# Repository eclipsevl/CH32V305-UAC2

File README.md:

# CH32V305-UAC2
ch32v305fbp6 + es9018k2m + opa1678 usb dac  

Due to using inexpensive components, the clock has approximately a 200 Hz error. Additionally, the MCLK GPIO speed exceeds the maximum 50 MHz limit at 192 kHz.  
If desired, you can use an external crystal for the I2S MCLK clock.  
This dac only support 48k,96k,192k 32bits, dsd and other formats are not considered.  
This DAC only supports high-speed connections.  
You might hear some popping sounds during sudden high-load tasks. I have added mute detection code to eliminate some of these occurrences. I hope it helps you. You can adjust your parameters in config.h.  

> [!NOTE]
> ch32v305fbp6 doesn't have OTG-HS(but it has OTG-FS), so you can't connect this project to a smartphone.  

## setup
Just flash HSDAC.elf to hardware. Don't use HID-Bootloader and dfu, they will be redoing in future.  

## help wanted
Can someone redesign the power amplifier circuit?  

# IMAGE

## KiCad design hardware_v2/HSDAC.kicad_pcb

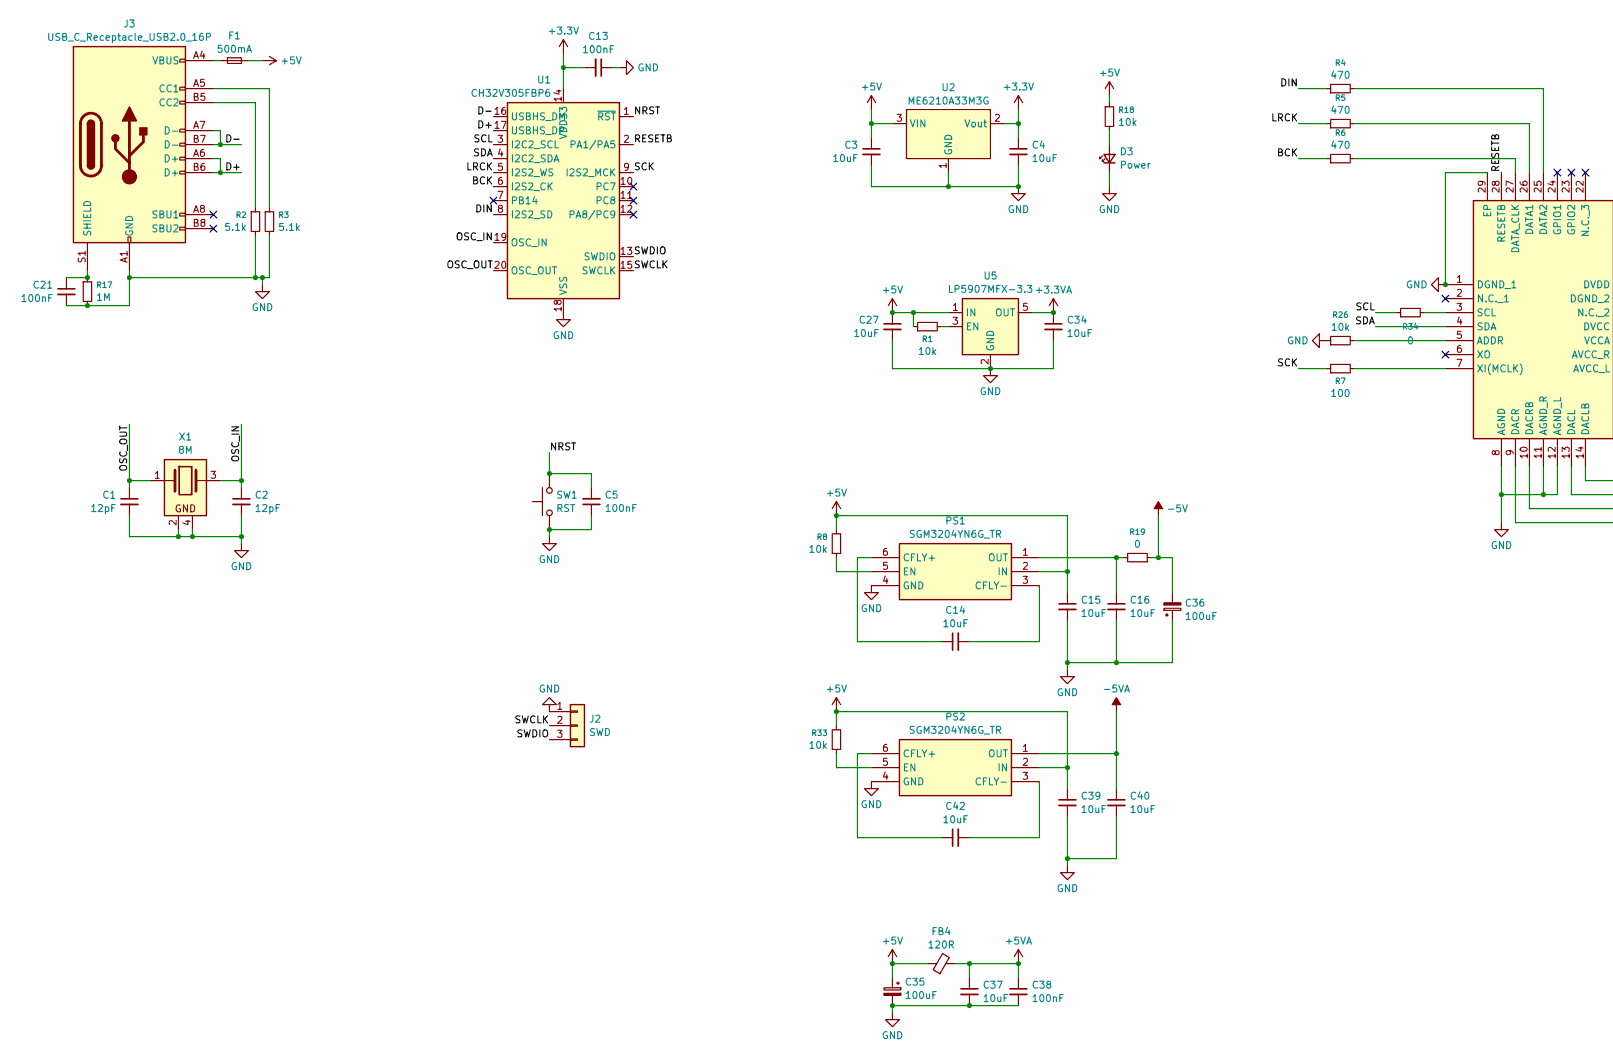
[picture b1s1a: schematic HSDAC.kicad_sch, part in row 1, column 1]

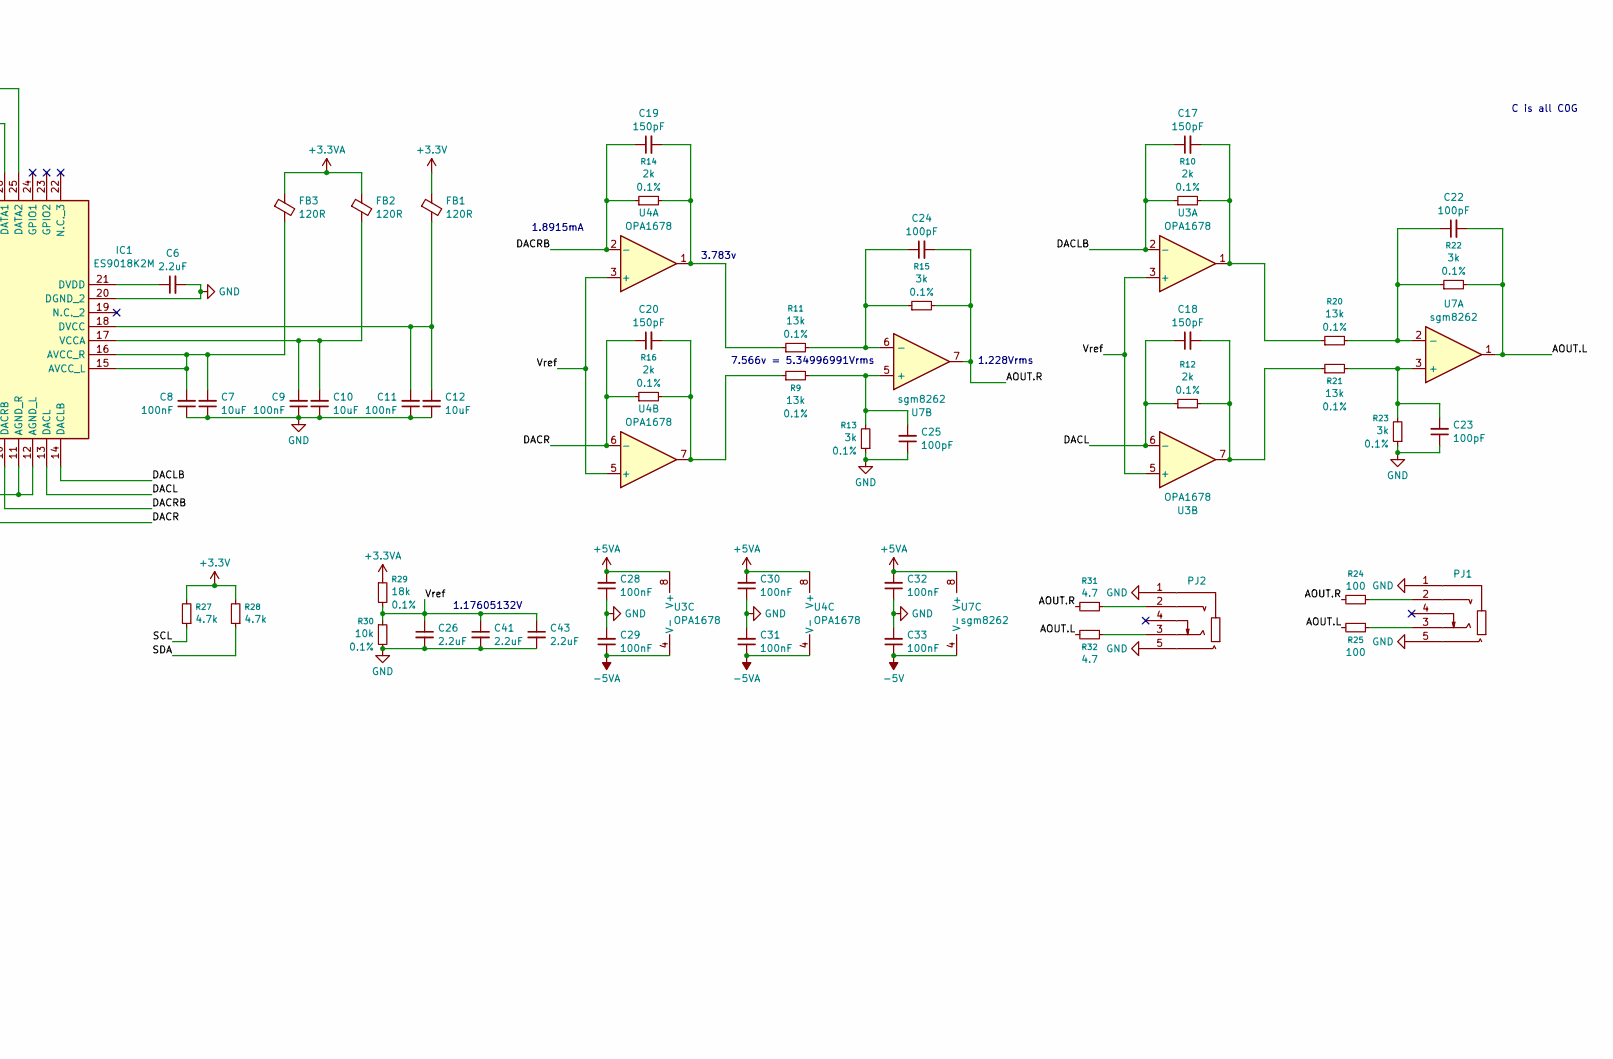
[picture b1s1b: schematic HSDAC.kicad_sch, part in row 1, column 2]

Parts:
C1, C2: 12pF; C0603
C3, C4, C7, C10, C12, C14, C15, C16, C27, C34, C37, C39, C40, C42: 10uF; C0603
C5, C8, C9, C11, C13, C21, C28, C29, C30, C31, C32, C33, C38: 100nF; C0603
C6, C26, C41, C43: 2.2uF; C0603
C17, C18, C19, C20: 150pF; C0603
C22, C23, C24, C25: 100pF; C0603
C35, C36: 100uF; CP_Elec_5x5.4
D3: Power; LED.0603
F1: 500mA; Fuse_0603_1608Metric
FB1, FB2, FB3, FB4: 120R; Ferrite_0603_1608Metric
IC1: ES9018K2M; QFN50P500X500X90-29N-D; Manufacturer_Part_Number ES9018K2M; Mouser Part Number 460-ES9018K2M
J2: SWD; JST_GH_SM03B-GHS-TB_1x03-1MP_P1.25mm_Horizontal
J3: USB_C_Receptacle_USB2.0_16P; USB_C_Receptacle_G-Switch_GT-USB-7010ASV
PJ1, PJ2: PJ327A; Manufacturer Part PJ-327A; LCSC Part Name PJ-327A
PS1, PS2: SGM3204YN6G_TR; SOT95P280X125-6N; Manufacturer_Part_Number SGM3204YN6G/TR
R1, R8, R18, R26, R30, R33: 10k; R0603
R2, R3: 5.1k; R0603
R4, R5, R6: 470; R0603
R7, R24, R25: 100; R0603
R9, R11, R20, R21: 13k; R0603
R10, R12, R14, R16: 2k; R0603
R13, R15, R22, R23: 3k; R0603
R17: 1M; R0603
R19, R34: 0; R0603
R27, R28: 4.7k; R0603
R29: 18k; R0603
R31, R32: 4.7; R0603
SW1: RST; 小龟轻触开关3_4_22.0MM
U1: CH32V305FBP6; TSSOP-20_4.4x6.5mm_P0.65mm
U2: ME6210A33M3G; SOT-23
U3, U4: OPA1678; SOIC-8_3.9x4.9mm_P1.27mm
U5: LP5907MFX-3.3; SOT-23-5
U7: sgm8262; SOIC-8_3.9x4.9mm_P1.27mm
X1: 8M; Crystal_SMD_3225-4Pin_3.2x2.5mm

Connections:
+3.3V: C4.1, C13.2, FB1.1, R27.2, R28.2, U1.14 (VDD33), U2.2 (Vout)
+3.3VA: C34.1, FB2.1, FB3.1, R29.1, U5.5 (OUT)
+5V: C3.1, C15.1, C27.1, C35.1, C39.1, F1.2, FB4.1, PS1.2 (IN), PS2.2 (IN), R1.1, R8.2, R18.1, R33.2, U2.3 (VIN), U5.1 (IN)
+5VA: C28.2, C30.2, C32.2, C37.1, C38.1, FB4.2, U3.8 (V+), U4.8 (V+), U7.8 (V+)
-5V: C33.1, C36.2, R19.1, U7.4 (V-)
-5VA: C29.1, C31.1, C40.1, PS2.1 (OUT), U3.4 (V-), U4.4 (V-)
/AOUT.L: C22.2, R22.2, R25.2, R32.2, U7.1
/AOUT.R: C24.2, R15.2, R24.2, R31.2, U7.7
/BCK: R6.1, U1.6 (I2S2_CK)
/D+: J3.A6 (D+), J3.B6 (D+), U1.17 (USBHS_DP)
/D-: J3.A7 (D-), J3.B7 (D-), U1.16 (USBHS_DM)
/DACL: C18.1, IC1.13 (DACL), R12.1, U3.6 (-)
/DACLB: C17.1, IC1.14 (DACLB), R10.1, U3.2 (-)
/DACR: C20.1, IC1.9 (DACR), R16.1, U4.6 (-)
/DACRB: C19.1, IC1.10 (DACRB), R14.1, U4.2 (-)
/DIN: R4.1, U1.8 (I2S2_SD)
/LRCK: R5.1, U1.5 (I2S2_WS)
/NRST: C5.2, SW1.2, U1.1 (~RST)
/OSC_IN: C2.1, U1.19 (OSC_IN), X1.3
/OSC_OUT: C1.1, U1.20 (OSC_OUT), X1.1
/RESETB: IC1.28 (RESETB), U1.2 (PA1/PA5)
/SCK: R7.1, U1.9 (I2S2_MCK)
/SCL: R27.1, R34.1, U1.3 (I2C2_SCL)
/SDA: IC1.4 (SDA), R28.1, U1.4 (I2C2_SDA)
/SWCLK: J2.2, U1.15 (SWCLK)
/SWDIO: J2.3, U1.13 (SWDIO)
/Vref: C26.1, C41.1, C43.1, R29.2, R30.1, U3.3 (+), U3.5 (+), U4.3 (+), U4.5 (+)
GND: C1.2, C2.2, C3.2, C4.2, C5.1, C6.2, C7.1, C8.1, C9.1, C10.1, C11.1, C12.1, C13.1, C15.2, C16.2, C21.2, C23.1, C25.1, C26.2, C27.2, C28.1, C29.2, C30.1, C31.2, C32.1, C33.2, C34.2, C35.2, C36.1, C37.2, C38.2, C39.2, C40.2, C41.2, C43.2, D3.1 (K), IC1.1 (DGND_1), IC1.8 (AGND), IC1.11 (AGND_R), IC1.12 (AGND_L), IC1.20 (DGND_2), IC1.29 (EP), J2.1, J3.A1 (GND), J3.A12 (GND), J3.B1 (GND), J3.B12 (GND), PJ1.1, PJ1.5, PJ2.1, PJ2.5, PS1.4 (GND), PS2.4 (GND), R2.2, R3.2, R13.1, R17.2, R23.1, R26.1, R30.2, SW1.1, U1.18 (VSS), U2.1 (GND), U5.2 (GND), X1.2, X1.4
unnamed: C17.2, R10.2, R20.1, U3.1
unnamed: C18.2, R12.2, R21.1, U3.7
unnamed: C19.2, R11.1, R14.2, U4.1
unnamed: C20.2, R9.1, R16.2, U4.7
unnamed: D3.2 (A), R18.2
unnamed: F1.1, J3.A4 (VBUS), J3.A9 (VBUS), J3.B4 (VBUS), J3.B9 (VBUS)
unnamed: IC1.5 (ADDR), R26.2
unnamed: C7.2, C8.2, FB3.2, IC1.15 (AVCC_L), IC1.16 (AVCC_R)
unnamed: IC1.26 (DATA1), R5.2
unnamed: IC1.25 (DATA2), R4.2
unnamed: IC1.27 (DATA_CLK), R6.2
unnamed: C11.2, C12.2, FB1.2, IC1.18 (DVCC)
unnamed: C6.1, IC1.21 (DVDD)
unnamed: IC1.3 (SCL), R34.2
unnamed: C9.2, C10.2, FB2.2, IC1.17 (VCCA)
unnamed: IC1.7 (XI(MCLK)), R7.2
unnamed: J3.A5 (CC1), R3.1
unnamed: J3.B5 (CC2), R2.1
unnamed: C21.1, J3.S1 (SHIELD), R17.1
unnamed: PJ1.2, R24.1
unnamed: PJ1.3, R25.1
unnamed: PJ2.2, R31.1
unnamed: PJ2.3, R32.1
unnamed: C14.1, PS1.6 (CFLY+)
unnamed: C14.2, PS1.3 (CFLY-)
unnamed: PS1.5 (EN), R8.1
unnamed: C16.1, PS1.1 (OUT), R19.2
unnamed: C42.1, PS2.6 (CFLY+)
unnamed: C42.2, PS2.3 (CFLY-)
unnamed: PS2.5 (EN), R33.1
unnamed: R1.2, U5.3 (EN)
unnamed: C23.2, R21.2, R23.2, U7.3 (+)
unnamed: C22.1, R20.2, R22.1, U7.2 (-)
unnamed: C25.2, R9.2, R13.2, U7.5 (+)
unnamed: C24.1, R11.2, R15.1, U7.6 (-)

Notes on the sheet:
3.783v
1.228Vrms
C is all C0G
7.566v = 5.34996991Vrms
1.8915mA
1.17605132V

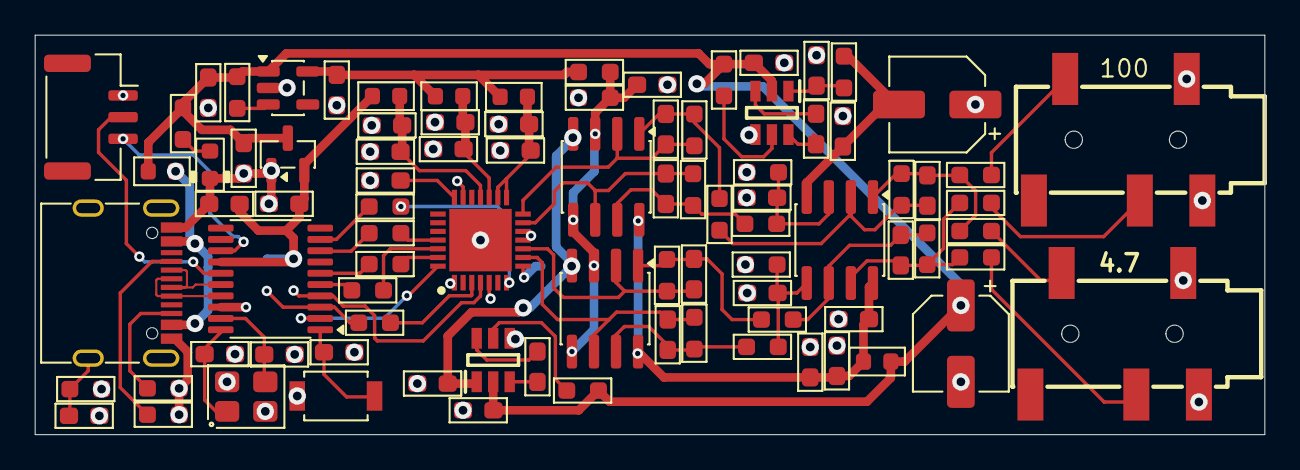
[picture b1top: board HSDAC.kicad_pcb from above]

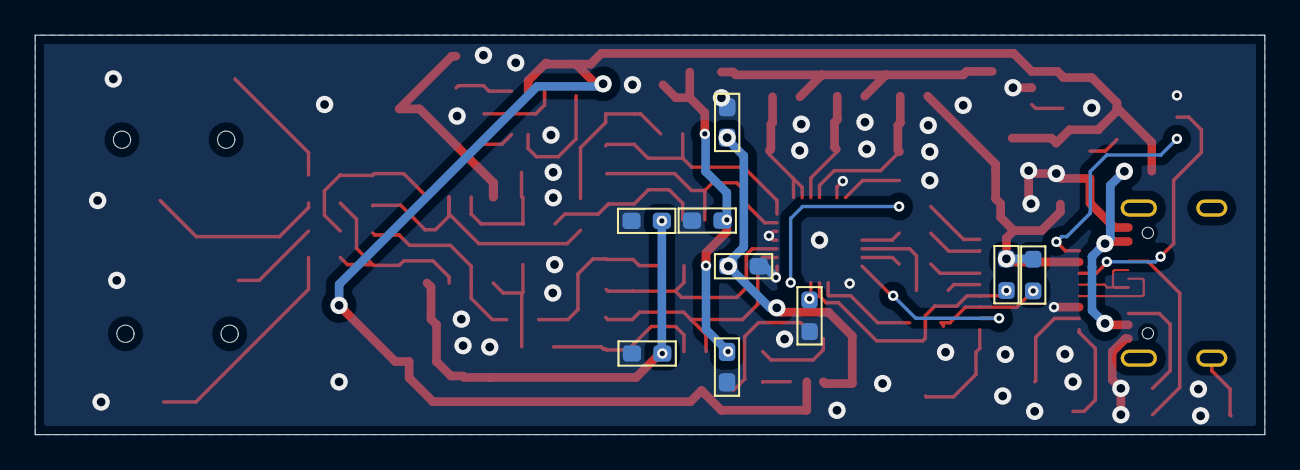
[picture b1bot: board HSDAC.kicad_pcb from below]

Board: 2 copper layers, 70.8 x 23.0 mm, 98 parts (9 on the bottom side), 63 nets.

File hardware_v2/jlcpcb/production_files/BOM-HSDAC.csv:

Comment,Designator,Footprint,LCSC,Quantity
2k,R16,R0603,,1
470,R5,R0603,,1
5.1k,R3,R0603,,1
100pF,C25,C0603,,1
150pF,C18,C0603,,1
2k,R14,R0603,,1
100pF,C24,C0603,,1
100,R25,R0603,,1
120R,FB2,Ferrite_0603_1608Metric,,1
100,R7,R0603,,1
120R,FB3,Ferrite_0603_1608Metric,,1
100nF,C9,C0603,,1
4.7k,R28,R0603,,1
500mA,F1,Fuse_0603_1608Metric,,1
10k,R8,R0603,,1
10uF,C27,C0603,,1
100nF,C30,C0603,,1
470,R4,R0603,,1
12pF,C1,C0603,,1
100nF,C13,C0603,,1
SGM3204YN6G_TR,PS1,SOT95P280X125-6N,,1
OPA1678,U4,SOIC-8_3.9x4.9mm_P1.27mm,,1
100pF,C22,C0603,,1
13k,R11,R0603,,1
10uF,C14,C0603,,1
100nF,C33,C0603,,1
100nF,C31,C0603,,1
10uF,C4,C0603,,1
100pF,C23,C0603,,1
150pF,C17,C0603,,1
13k,R21,R0603,,1
10uF,C7,C0603,,1
~,PJ1,PJ327A,,1
10uF,C12,C0603,,1
3k,R23,R0603,,1
3k,R22,R0603,,1
100nF,C5,C0603,,1
2k,R12,R0603,,1
100,R24,R0603,,1
13k,R20,R0603,,1
150pF,C19,C0603,,1
100nF,C29,C0603,,1
100nF,C11,C0603,,1
Power,D3,LED.0603,,1
120R,FB1,Ferrite_0603_1608Metric,,1
10uF,C10,C0603,,1
3k,R13,R0603,,1
4.7k,R27,R0603,,1
10k,R26,R0603,,1
2k,R10,R0603,,1
5.1k,R2,R0603,,1
13k,R9,R0603,,1
RST,SW1,小龟轻触开关3_4_22.0MM,,1
12pF,C2,C0603,,1
USB_C_Receptacle_USB2.0_16P,J3,USB_C_Receptacle_G-Switch_GT-USB-7010ASV,,1
470,R6,R0603,,1
2.2uF,C6,C0603,,1
10k,R18,R0603,,1
100nF,C32,C0603,,1
2.2uF,C26,C0603,,1
10uF,C16,C0603,,1
ME6210A33M3G,U2,SOT-23,,1
10k,R1,R0603,,1
8M,X1,Crystal_SMD_3225-4Pin_3.2x2.5mm,,1
100nF,C8,C0603,,1
10uF,C15,C0603,,1
100nF,C28,C0603,,1
CH32V305FBP6,U1,TSSOP-20_4.4x6.5mm_P0.65mm,,1
3k,R15,R0603,,1
150pF,C20,C0603,,1
10uF,C3,C0603,,1
ES9018K2M,IC1,QFN50P500X500X90-29N-D,,1
OPA1678,U3,SOIC-8_3.9x4.9mm_P1.27mm,,1
LP5907MFX-3.3,U5,SOT-23-5,,1
10uF,C34,C0603,,1
100nF,C38,C0603,,1
18k,R29,R0603,,1
4.7,R31,R0603,,1
100uF,C36,CP_Elec_5x5.4,,1
SGM3204YN6G_TR,PS2,SOT95P280X125-6N,,1
10k,R33,R0603,,1
0,R19,R0603,,1
100uF,C35,CP_Elec_5x5.4,,1
120R,FB4,Ferrite_0603_1608Metric,,1
0,R34,R0603,,1
sgm8262,U7,SOIC-8_3.9x4.9mm_P1.27mm,,1
10uF,C37,C0603,,1
10uF,C42,C0603,,1
4.7,R32,R0603,,1
10k,R30,R0603,,1
100nF,C21,C0603,,1
~,PJ2,PJ327A,,1
1M,R17,R0603,,1
SWD,J2,JST_GH_SM03B-GHS-TB_1x03-1MP_P1.25mm_Horizontal,,1
10uF,C39,C0603,,1
10uF,C40,C0603,,1
2.2uF,C43,C0603,,1
2.2uF,C41,C0603,,1

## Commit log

2025-07-06 fix exception when upload firmware
2025-12-23 refactor version 1
2025-12-23 set es9018 using interrupt
2025-12-24 feat: slience DAC when pc send incontinue data when doing high cpu load task
2025-12-24 Revise README for clarity and additional details
    Updated README with improved clarity and additional information on DAC usage and issues.
2026-01-11 remove slience detect module feat: add ability to process audio in main thread
2026-01-15 Update README with setup instructions and formatting
    Added setup instructions and improved formatting.
2026-03-06 Update README with additional information and formatting
    Added note about OTG-FS limitation for ch32v305fbp6.
2026-03-11 add hardware v2
